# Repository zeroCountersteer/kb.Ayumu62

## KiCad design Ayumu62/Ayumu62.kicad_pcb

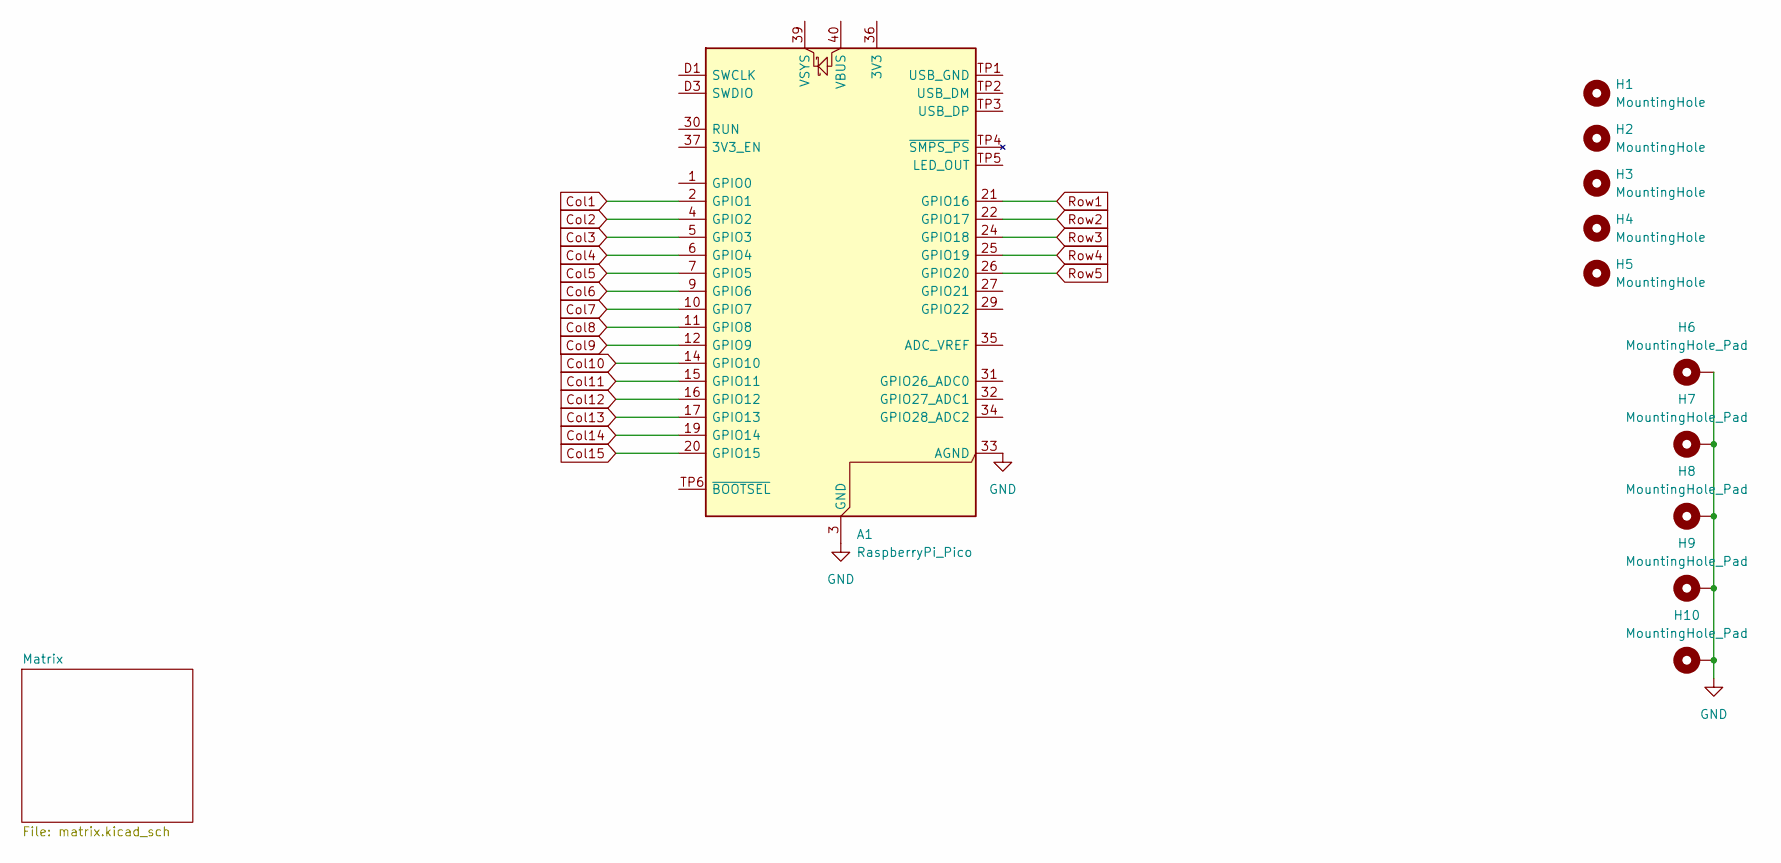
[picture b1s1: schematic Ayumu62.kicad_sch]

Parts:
A1: RaspberryPi_Pico; RaspberryPi_Pico_Common_Unspecified
H1, H2, H3, H4, H5: MountingHole; Stabilizer_Cherry_MX_2.00u
H6, H7, H8, H9, H10: MountingHole_Pad; MountingHole_2.2mm_M2_DIN965_Pad

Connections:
Col1: A1.2 (GPIO1)
Col2: A1.4 (GPIO2); also elsewhere on the board
Col3: A1.5 (GPIO3); also elsewhere on the board
Col4: A1.6 (GPIO4); also elsewhere on the board
Col5: A1.7 (GPIO5); also elsewhere on the board
Col6: A1.9 (GPIO6); also elsewhere on the board
Col7: A1.10 (GPIO7); also elsewhere on the board
Col8: A1.11 (GPIO8); also elsewhere on the board
Col9: A1.12 (GPIO9); also elsewhere on the board
Col10: A1.14 (GPIO10); also elsewhere on the board
Col11: A1.15 (GPIO11); also elsewhere on the board
Col12: A1.16 (GPIO12); also elsewhere on the board
Col13: A1.17 (GPIO13); also elsewhere on the board
Col14: A1.19 (GPIO14); also elsewhere on the board
Col15: A1.20 (GPIO15); also elsewhere on the board
GND: A1.3 (GND), A1.8 (GND), A1.13 (GND), A1.18 (GND), A1.23 (GND), A1.28 (GND), A1.33 (AGND), A1.38 (GND), A1.D2 (GND), H6.1, H7.1, H8.1, H9.1, H10.1
Row1: A1.21 (GPIO16); also elsewhere on the board
Row2: A1.22 (GPIO17); also elsewhere on the board
Row3: A1.24 (GPIO18); also elsewhere on the board
Row4: A1.25 (GPIO19); also elsewhere on the board
Row5: A1.26 (GPIO20); also elsewhere on the board

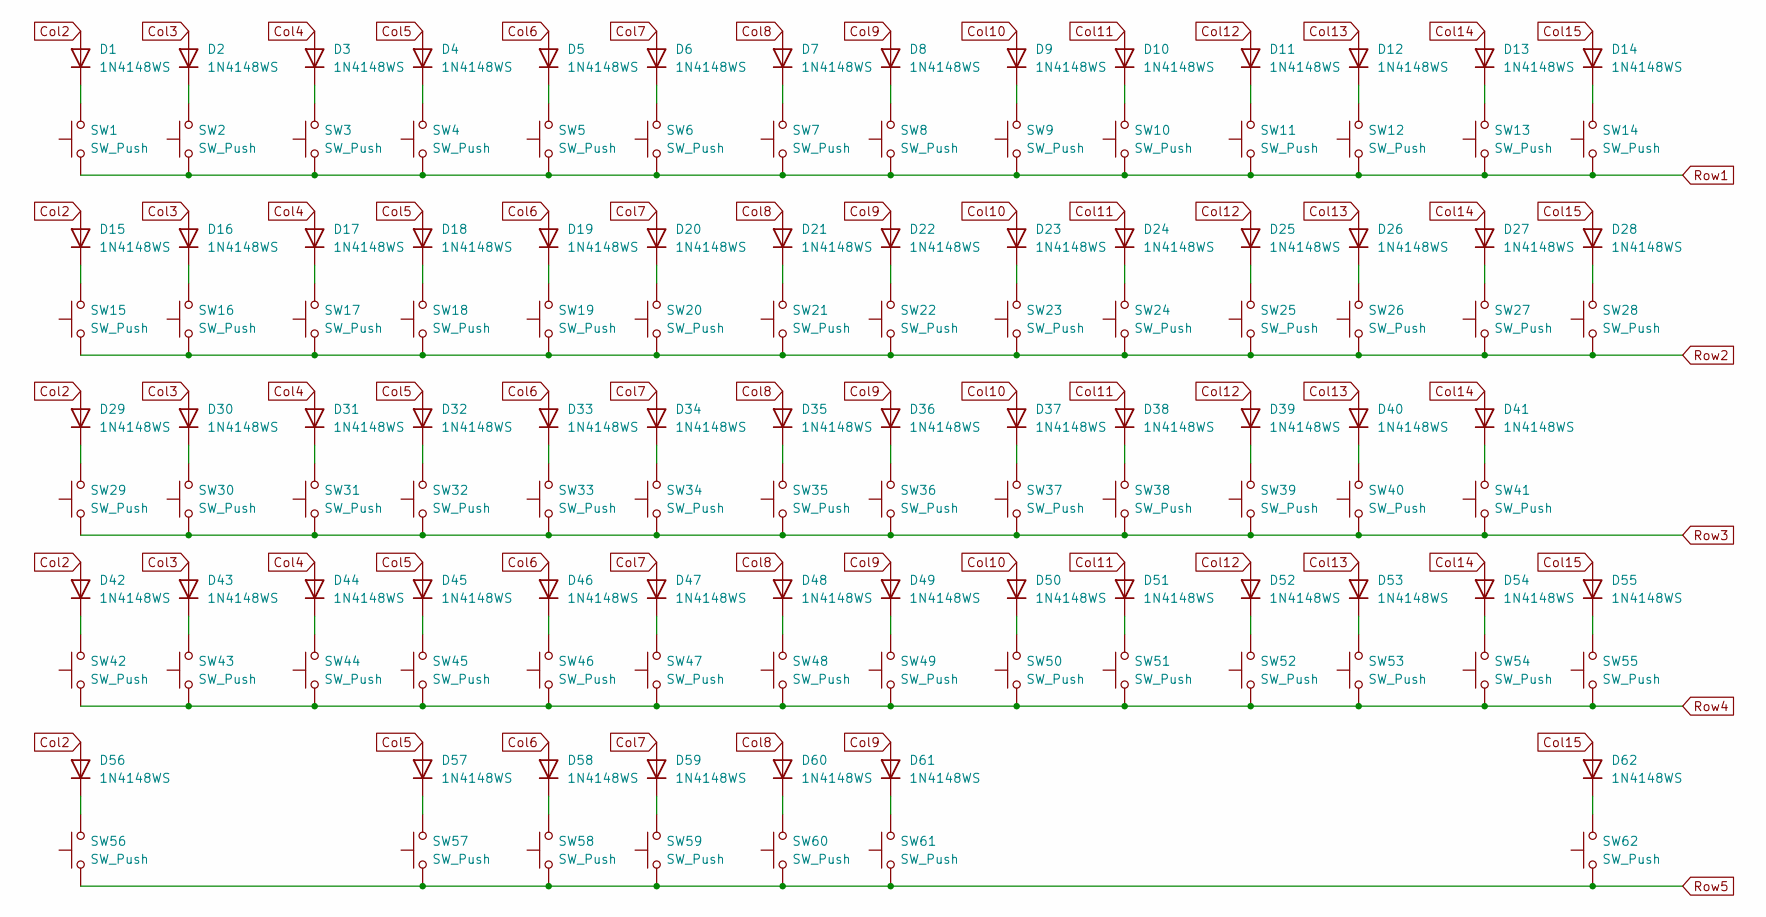
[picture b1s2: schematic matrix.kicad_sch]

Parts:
D1, D2, D3, D4, D5, D6, D7, D8, D9, D10, D11, D12, D13, D14, D15, D16, D17, D18, D19, D20, D21, D22, D23, D24, D25, D26, D27, D28, D29, D30, D31, D32, D33, D34, D35, D36, D37, D38, D39, D40, D41, D42, D43, D44, D45, D46, D47, D48, D49, D50, D51, D52, D53, D54, D55, D56, D57, D58, D59, D60, D61, D62: 1N4148WS; D_SOD-323
SW1, SW2, SW3, SW4, SW5, SW7, SW9, SW10, SW11, SW14, SW15, SW16, SW19, SW20, SW21, SW23, SW26, SW27, SW28, SW29, SW30, SW31, SW32, SW33, SW34, SW35, SW36, SW37, SW38, SW39, SW40, SW41, SW45, SW46, SW47, SW48, SW49, SW50, SW51, SW52, SW53, SW54, SW55, SW56, SW57, SW58, SW59, SW60: SW_Push; SW_Hotswap_Kailh_MX_Plated_1.00u
SW6, SW42: SW_Push; SW_Hotswap_Kailh_MX_Plated_2.00u
SW8, SW12, SW24, SW25, SW44, SW62: SW_Push; SW_Hotswap_Kailh_MX_Plated_1.50u
SW13, SW22: SW_Push; SW_Hotswap_Kailh_MX_Plated_1.75u
SW17, SW18: SW_Push; SW_Hotswap_Kailh_MX_Plated_2.25u
SW43: SW_Push; SW_Hotswap_Kailh_MX_Plated_1.25u
SW61: SW_Push; SW_Hotswap_Kailh_MX_Plated_2.75u

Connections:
Col2: D1.2 (A), D15.2 (A), D29.2 (A), D42.2 (A), D56.2 (A); also elsewhere on the board
Col3: D2.2 (A), D16.2 (A), D30.2 (A), D43.2 (A); also elsewhere on the board
Col4: D3.2 (A), D17.2 (A), D31.2 (A), D44.2 (A); also elsewhere on the board
Col5: D4.2 (A), D18.2 (A), D32.2 (A), D45.2 (A), D57.2 (A); also elsewhere on the board
Col6: D5.2 (A), D19.2 (A), D33.2 (A), D46.2 (A), D58.2 (A); also elsewhere on the board
Col7: D6.2 (A), D20.2 (A), D34.2 (A), D47.2 (A), D59.2 (A); also elsewhere on the board
Col8: D7.2 (A), D21.2 (A), D35.2 (A), D48.2 (A), D60.2 (A); also elsewhere on the board
Col9: D8.2 (A), D22.2 (A), D36.2 (A), D49.2 (A), D61.2 (A); also elsewhere on the board
Col10: D9.2 (A), D23.2 (A), D37.2 (A), D50.2 (A); also elsewhere on the board
Col11: D10.2 (A), D24.2 (A), D38.2 (A), D51.2 (A); also elsewhere on the board
Col12: D11.2 (A), D25.2 (A), D39.2 (A), D52.2 (A); also elsewhere on the board
Col13: D12.2 (A), D26.2 (A), D40.2 (A), D53.2 (A); also elsewhere on the board
Col14: D13.2 (A), D27.2 (A), D41.2 (A), D54.2 (A); also elsewhere on the board
Col15: D14.2 (A), D28.2 (A), D55.2 (A), D62.2 (A); also elsewhere on the board
unnamed: D1.1 (K), SW1.2
unnamed: D2.1 (K), SW2.2
unnamed: D3.1 (K), SW3.2
unnamed: D4.1 (K), SW4.2
unnamed: D5.1 (K), SW5.2
unnamed: D6.1 (K), SW6.2
unnamed: D7.1 (K), SW7.2
unnamed: D8.1 (K), SW8.2
unnamed: D9.1 (K), SW9.2
unnamed: D10.1 (K), SW10.2
unnamed: D11.1 (K), SW11.2
unnamed: D12.1 (K), SW12.2
unnamed: D13.1 (K), SW13.2
unnamed: D14.1 (K), SW14.2
unnamed: D15.1 (K), SW15.2
unnamed: D16.1 (K), SW16.2
unnamed: D17.1 (K), SW17.2
unnamed: D18.1 (K), SW18.2
unnamed: D19.1 (K), SW19.2
unnamed: D20.1 (K), SW20.2
unnamed: D21.1 (K), SW21.2
unnamed: D22.1 (K), SW22.2
unnamed: D23.1 (K), SW23.2
unnamed: D24.1 (K), SW24.2
unnamed: D25.1 (K), SW25.2
unnamed: D26.1 (K), SW26.2
unnamed: D27.1 (K), SW27.2
unnamed: D28.1 (K), SW28.2
unnamed: D29.1 (K), SW29.2
unnamed: D30.1 (K), SW30.2
unnamed: D31.1 (K), SW31.2
unnamed: D32.1 (K), SW32.2
unnamed: D33.1 (K), SW33.2
unnamed: D34.1 (K), SW34.2
unnamed: D35.1 (K), SW35.2
unnamed: D36.1 (K), SW36.2
unnamed: D37.1 (K), SW37.2
unnamed: D38.1 (K), SW38.2
unnamed: D39.1 (K), SW39.2
unnamed: D40.1 (K), SW40.2
unnamed: D41.1 (K), SW41.2
unnamed: D42.1 (K), SW42.2
unnamed: D43.1 (K), SW43.2
unnamed: D44.1 (K), SW44.2
unnamed: D45.1 (K), SW45.2
unnamed: D46.1 (K), SW46.2
unnamed: D47.1 (K), SW47.2
unnamed: D48.1 (K), SW48.2
unnamed: D49.1 (K), SW49.2
unnamed: D50.1 (K), SW50.2
unnamed: D51.1 (K), SW51.2
unnamed: D52.1 (K), SW52.2
unnamed: D53.1 (K), SW53.2
unnamed: D54.1 (K), SW54.2
unnamed: D55.1 (K), SW55.2
unnamed: D56.1 (K), SW56.2
unnamed: D57.1 (K), SW57.2
unnamed: D58.1 (K), SW58.2
unnamed: D59.1 (K), SW59.2
unnamed: D60.1 (K), SW60.2
unnamed: D61.1 (K), SW61.2
unnamed: D62.1 (K), SW62.2
Row1: SW1.1, SW2.1, SW3.1, SW4.1, SW5.1, SW6.1, SW7.1, SW8.1, SW9.1, SW10.1, SW11.1, SW12.1, SW13.1, SW14.1; also elsewhere on the board
Row2: SW15.1, SW16.1, SW17.1, SW18.1, SW19.1, SW20.1, SW21.1, SW22.1, SW23.1, SW24.1, SW25.1, SW26.1, SW27.1, SW28.1; also elsewhere on the board
Row3: SW29.1, SW30.1, SW31.1, SW32.1, SW33.1, SW34.1, SW35.1, SW36.1, SW37.1, SW38.1, SW39.1, SW40.1, SW41.1; also elsewhere on the board
Row4: SW42.1, SW43.1, SW44.1, SW45.1, SW46.1, SW47.1, SW48.1, SW49.1, SW50.1, SW51.1, SW52.1, SW53.1, SW54.1, SW55.1; also elsewhere on the board
Row5: SW56.1, SW57.1, SW58.1, SW59.1, SW60.1, SW61.1, SW62.1; also elsewhere on the board

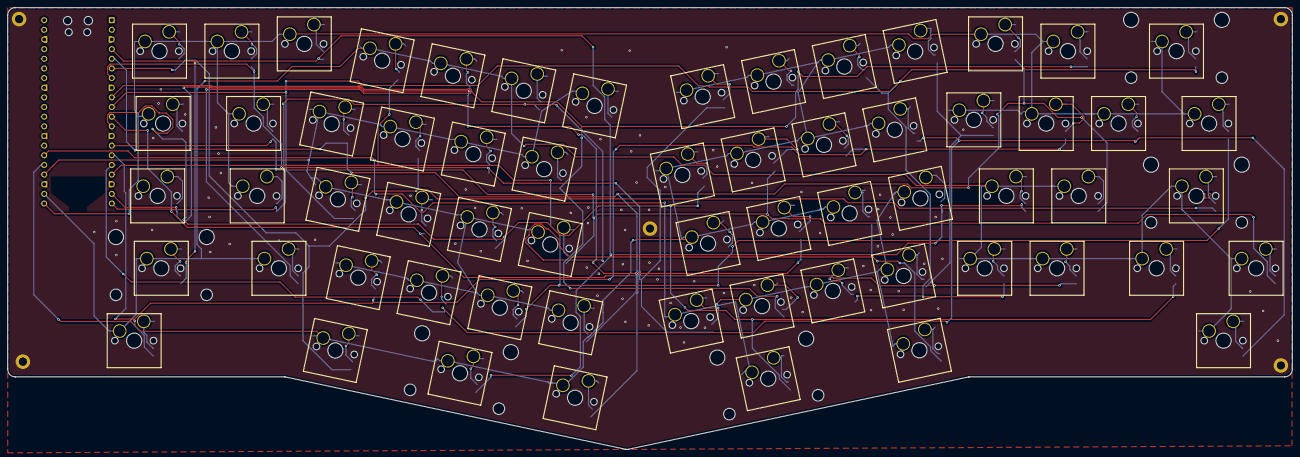
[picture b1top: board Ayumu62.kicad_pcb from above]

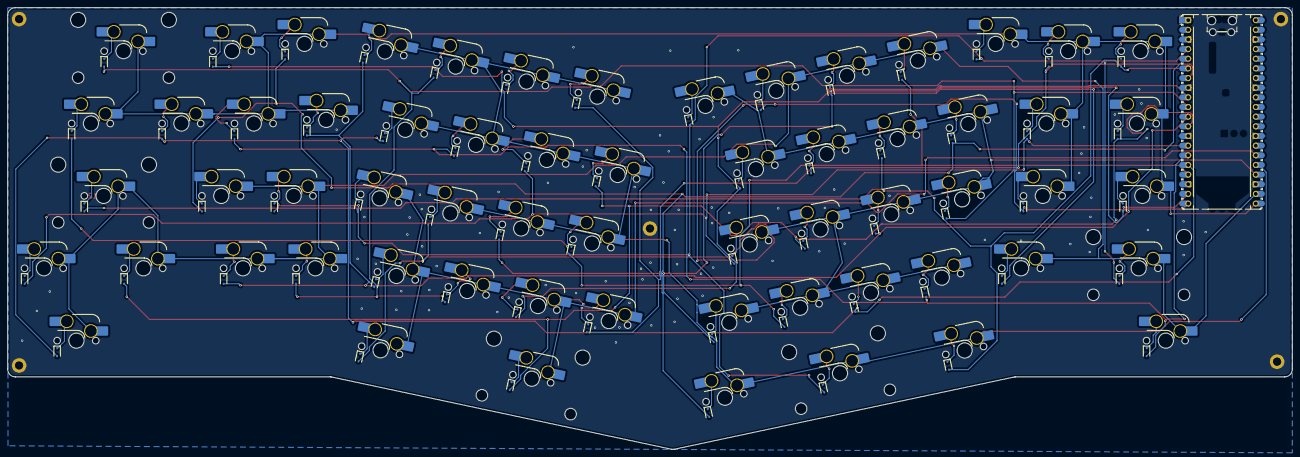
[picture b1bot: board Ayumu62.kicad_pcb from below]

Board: 2 copper layers, 338.1 x 116.2 mm, 135 parts (63 on the bottom side), 82 nets.
